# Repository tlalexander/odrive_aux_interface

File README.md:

Meow I'm a cat.

This repo contains Kicad files for an Odrive auxiliary interface board.

This board plugs in to your Odrive and gives you JST-XH connectors for the GPIO.

This is version 1.2 (see previous commits for older versions).
1.2 uses an ethernet cable and RS-485 for interface for communications.
1.2 also features an e-stop circuit which must be driven by a square wave.

See parts_list.txt for a parts list for the older V1.1. See the current schematic for part info on 1.2.

Order the older V1.1 PCB directly from OSHPark here:
https://oshpark.com/shared_projects/oXQvdpD9

This board was designed by Taylor Alexander for Twisted Fields LLC.
Big thanks to Daniel Theobald for funding the work.

This work is licensed CC0 aka Public Domain. Use this information for any purpose.

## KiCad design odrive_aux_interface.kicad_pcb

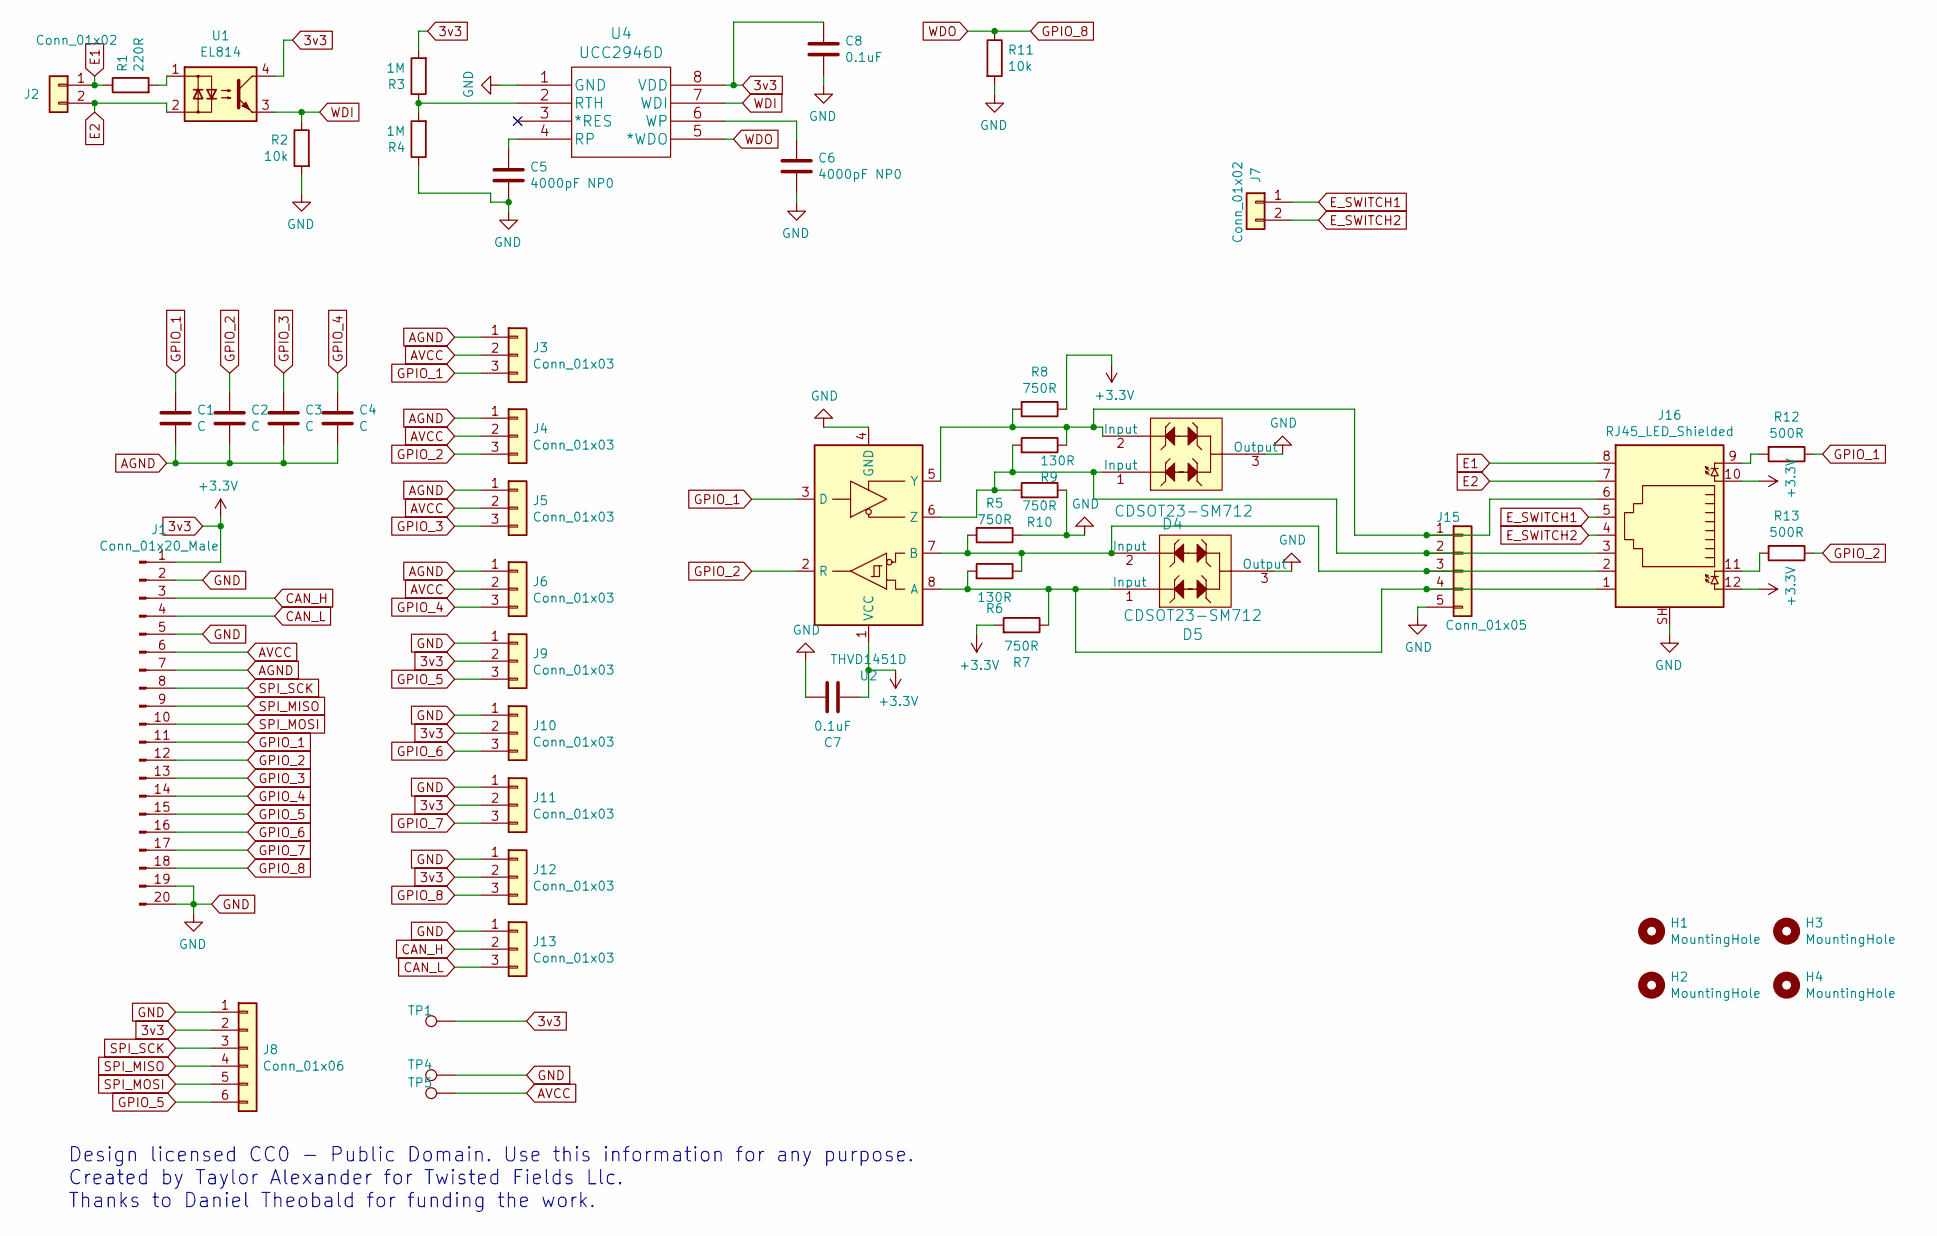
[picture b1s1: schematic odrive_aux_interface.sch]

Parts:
C1, C2, C3, C4: C; C_0805_2012Metric
C5, C6: 4000pF NP0; C_0805_2012Metric
C7, C8: 0.1uF; C_0805_2012Metric
D4, D5: CDSOT23-SM712; SOT-23-3; MPN CDSOT23-SM712; Digikey CDSOT23-SM712CT-ND
H1, H2, H3, H4: MountingHole; MountingHole_3.2mm_M3
J1: Conn_01x20_Male; PinHeader_1x20_P2.54mm_Vertical
J2, J7: Conn_01x02; JST_XH_B2B-XH-A_1x02_P2.50mm_Vertical
J3, J4, J5, J6, J9, J10, J11, J12, J13: Conn_01x03; JST_XH_B3B-XH-A_1x03_P2.50mm_Vertical
J8: Conn_01x06; JST_XH_B6B-XH-A_1x06_P2.50mm_Vertical
J15: Conn_01x05; JST_XH_B5B-XH-A_1x05_P2.50mm_Vertical; Digikey 455-1707-ND
J16: RJ45_LED_Shielded; RJ45_Amphenol_RJHSE538X
R1: 220R; R_0805_2012Metric
R2, R11: 10k; R_0805_2012Metric
R3, R4: 1M; R_0805_2012Metric
R5, R7, R8, R10: 750R; R_0805_2012Metric; Digikey RMCF0805FT750RCT-ND
R6, R9: 130R; R_0805_2012Metric; Digikey RMCF0805FT130RCT-ND
R12, R13: 500R; R_0805_2012Metric; Digikey RMCF0805FT750RCT-ND
TP1, TP4, TP5: TestPoint; TestPoint_Keystone_5015_Micro-Minature
U1: EL814; SO-4_7.6x3.6mm_P2.54mm
U2: THVD1451D; SOIC-8_3.9x4.9mm_P1.27mm; Digikey 296-THVD1451D-ND
U4: UCC2946D; SO-8_3.9x4.9mm_P1.27mm

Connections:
3v3: C7.1, C8.1, J1.1, J8.2, J9.2, J10.2, J11.2, J12.2, J16.10, J16.12, R3.2, R7.2, R8.1, TP1.1, U1.4, U2.1 (VCC), U4.8 (VDD)
AGND: C1.2, C2.2, C3.2, C4.2, J1.7, J3.1, J4.1, J5.1, J6.1
AVCC: J1.6, J3.2, J4.2, J5.2, J6.2, TP5.1
CAN_H: J1.3, J13.2
CAN_L: J1.4, J13.3
E1: J2.1, J16.8, R1.1
E2: J2.2, J16.7, U1.2
E_SWITCH1: J7.1, J16.5
E_SWITCH2: J7.2, J16.4
GND: C5.2, C6.2, C7.2, C8.2, D4.3 (Output), D5.3 (Output), J1.2, J1.5, J1.19, J1.20, J8.1, J9.1, J10.1, J11.1, J12.1, J13.1, J15.5, J16.SH, R2.2, R4.1, R5.1, R10.1, R11.2, TP4.1, U2.4 (GND), U4.1 (GND)
GPIO_1: C1.1, J1.11, J3.3, R12.1, U2.3 (D)
GPIO_2: C2.1, J1.12, J4.3, R13.1, U2.2 (R)
GPIO_3: C3.1, J1.13, J5.3
GPIO_4: C4.1, J1.14, J6.3
GPIO_5: J1.15, J8.6, J9.3
GPIO_6: J1.16, J10.3
GPIO_7: J1.17, J11.3
GPIO_8: J1.18, J12.3, R11.1, U4.5 (*WDO)
unnamed: C5.1, U4.4 (RP)
unnamed: C6.1, U4.6 (WP)
unnamed: D4.1 (Input), J15.2, J16.3, R9.2, R10.2, U2.6 (Z)
unnamed: D4.2 (Input), J15.1, J16.6, R8.2, R9.1, U2.5 (Y)
unnamed: D5.1 (Input), J15.4, J16.1, R6.2, R7.1, U2.8 (A)
unnamed: D5.2 (Input), J15.3, J16.2, R5.2, R6.1, U2.7 (B)
unnamed: J16.9, R12.2
unnamed: J16.11, R13.2
unnamed: R1.2, U1.1
unnamed: R3.1, R4.2, U4.2 (RTH)
SPI_MISO: J1.9, J8.4
SPI_MOSI: J1.10, J8.5
SPI_SCK: J1.8, J8.3
WDI: R2.1, U1.3, U4.7 (WDI)

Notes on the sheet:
Design licensed CC0 - Public Domain. Use this information for any purpose. Created by Taylor Alexander for Twisted Fields Llc. Thanks to Daniel Theobald for funding the work.

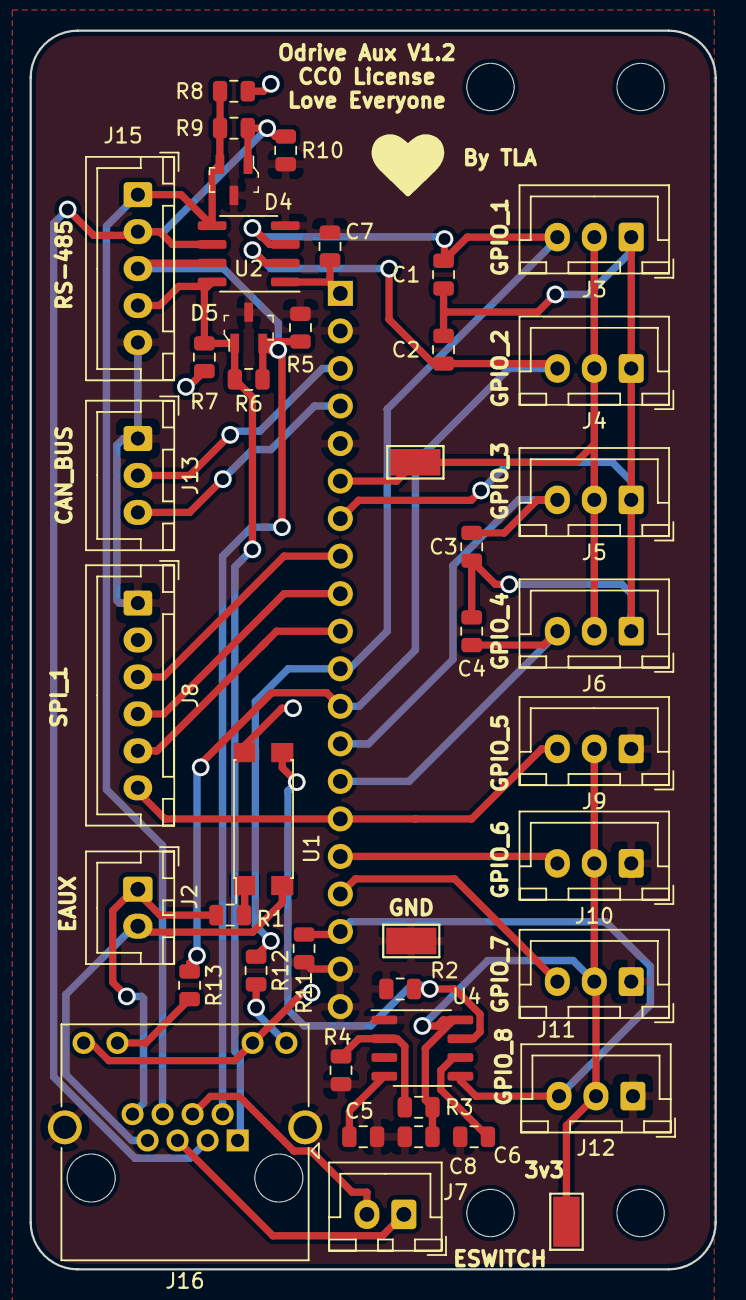
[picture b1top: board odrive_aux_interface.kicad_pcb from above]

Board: 2 copper layers, 46.4 x 83.8 mm, 48 parts (1 on the bottom side), 32 nets.

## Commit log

2019-10-24 Initial Commit.
2020-06-12 Update to v1.2, add gerbers.

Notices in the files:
odrive_aux_interface.kicad_pcb:
CC0 License
